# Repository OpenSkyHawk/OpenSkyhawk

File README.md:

```
  ____                ______        __ __            __  
 / __ \___  ___ ___  / __/ /____ __/ // /__ __    __/ /__
/ /_/ / _ \/ -_) _ \_\ \/  '_/ // / _  / _ `/ |/|/ /  '_/
\____/ .__/\__/_//_/___/_/\_\\_, /_//_/\_,_/|__,__/_/\_\ 
    /_/                     /___/                        
          ── DCS A-4E Skyhawk Home Cockpit ──
```

Physical DCS A-4E Skyhawk home cockpit — 3D-printed panels, custom PCBs, and STM32 firmware for the [DCS A-4E Community Mod](https://github.com/Community-A-4E/community-a4e-c). Controllers communicate over CAN bus.

## Repository Structure

```
OpenSkyhawk/
├── CAD/                        # Fusion 360 source files (.f3d); STLs gitignored
│   ├── Center_Console/
│   ├── Left_Console/
│   ├── Right_Console/
│   └── Shared/                 # Common brackets, mounting fixtures
│
├── PCB/                        # KiCad projects, one folder per board
│   ├── Center_Console/
│   │   └── Center_Armament/
│   │       ├── Armament_MCU/   # Main STM32 board
│   │       ├── AWRS_Panel/     # Breakout board
│   │       └── Misc_Switch_Panel/
│   ├── Left_Console/
│   ├── Right_Console/
│   └── Libraries/              # Shared KiCad symbols and footprints
│
├── Firmware/                   # PlatformIO projects
│   ├── Panels/                 # Production sketches, one folder per node
│   ├── Templates/              # Starting points for new sketches
│   ├── Examples/               # Bench and end-to-end test sketches
│   └── Libraries/              # Shared firmware code
│
└── docs/
    ├── References/             # Cockpit photos, manuals, screenshots
    ├── Datasheets/             # Component datasheets
    └── claude/                 # AI-readable architecture and standards docs
```

## Architecture

Each physical panel group is driven by one **STM32F103CBT6** MCU board. Boards communicate over **CAN bus** via Molex Mini-Fit Jr connectors. Panel breakout boards connect to their MCU board via 6- or 8-pin JST-XH harnesses. Firmware is built with **PlatformIO**.

DCS communication: DCS-BIOS cockpit state flows PC → USB CDC → RP2040 bridge (Tiny2040) → UART → STM32 CAN master → CAN bus → all avionics nodes. STM32 native USB CDC is not used — it crashes under sustained DCS-BIOS load.

## Console Layout

| Console | Panels |
|---------|--------|
| Center Console | Armament, AWRS, Misc Switches, main flight instruments |
| Left Console | ECM, fuel, electrical systems |
| Right Console | Radios, nav |

## Hardware Notes

### Screw Standards

| Size | Use |
|------|-----|
| M2 | PCB mounts, small standoffs |
| M3 | Placards, light rings, small brackets |
| M4 | Instrument bezels, gauge mounting — clearance Ø4.3–4.5 mm |
| M5 | Panel-to-subpanel, corner mounts — clearance Ø5.3–5.5 mm |

### Switch Sizing

- Toggle switches: 12 mm (standard panels), ~6 mm (ECM modules)

### Gauges

- LOX gauge: 2-5/8″ (~67 mm total)
- Radar Altimeter: 3-1/8″ (~100 mm total with bezel)

## Licensing

Copyright (c) 2026 OpenSkyHawk.

| Layer | License |
|-------|---------|
| CAD, PCB, Docs | CC BY-NC-SA 4.0 — root [LICENSE](./LICENSE) |
| Firmware | GPL v2 (DCS-BIOS dependency) — [Firmware/LICENSE](./Firmware/LICENSE) |

GitHub's repo-level badge reflects the root `LICENSE` (CC BY-NC-SA 4.0); the
firmware is GPL v2 under `Firmware/LICENSE`.

## References

- [Open Hornet Hardware](https://github.com/jrsteensen/OpenHornet)
- [Open Hornet Software](https://github.com/jrsteensen/OpenHornet-Software)
- [The Warthog Project](https://thewarthogproject.com/)
- [Viperpits](https://www.viperpits.org/smf/index.php)
- [The Skyhawk Association — Cockpit](https://skyhawk.org/page/skyhawk-cockpit)

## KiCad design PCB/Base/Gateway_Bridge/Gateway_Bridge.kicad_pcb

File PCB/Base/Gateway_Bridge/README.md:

# Gateway_Bridge — Gateway/Bridge board (SimGateway + PanelBridge)

**Status: In progress** — not released yet.

A board is released only once it has been built, brought up, and verified: it is then listed in `PCB/manifest.yaml` and ships in the next hardware release (`hardware-vX.Y.Z`, see the repository's Releases). The model is design decision D10; the release standard is the *Releases* section of `docs/_source/hardware-standards.md`.

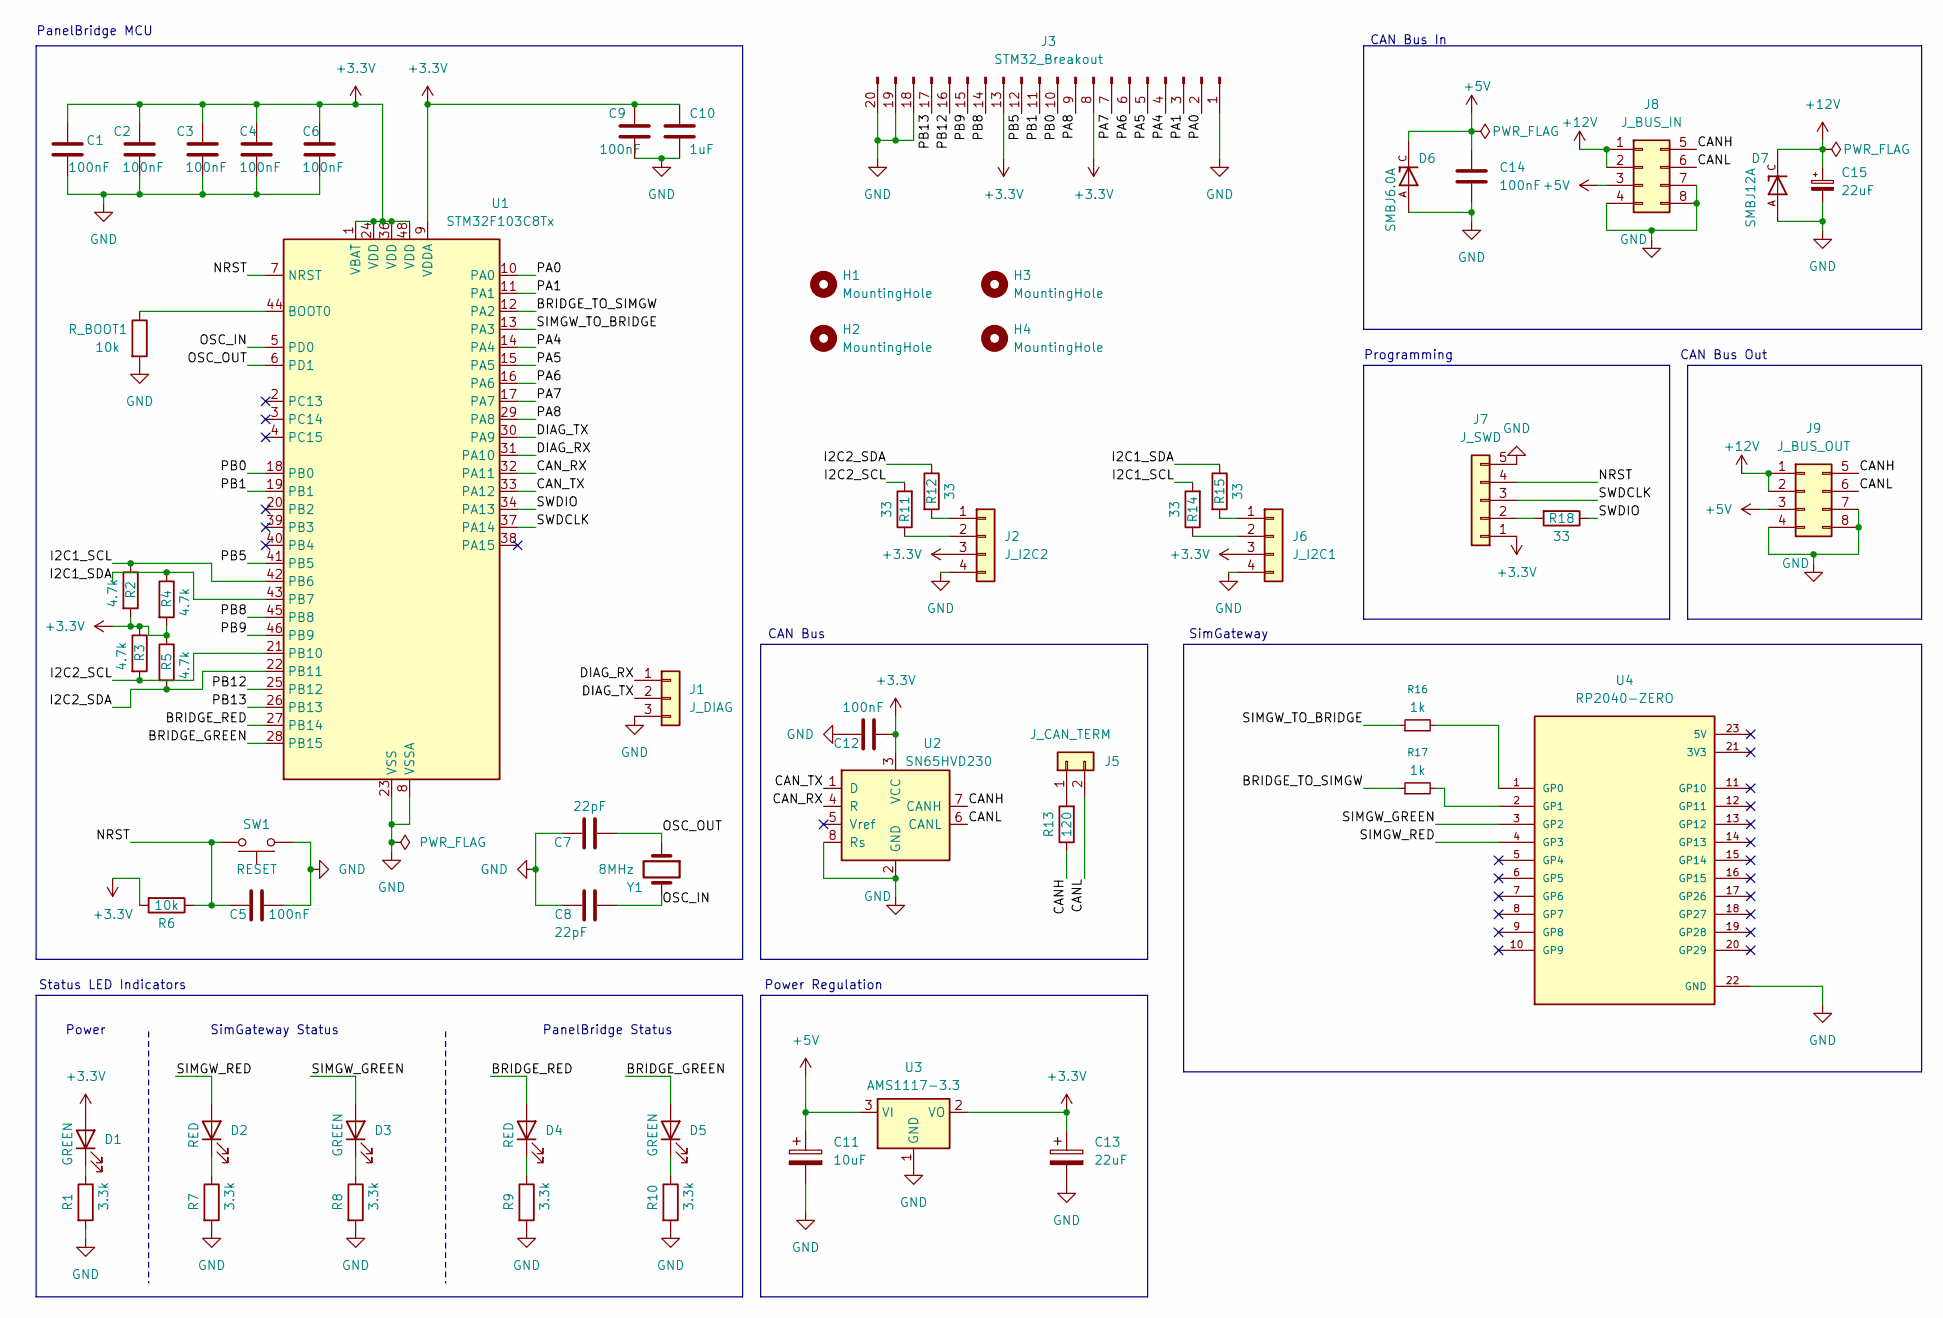
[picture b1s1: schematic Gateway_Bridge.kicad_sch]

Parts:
C1, C2, C3, C4, C5, C6, C9, C12, C14: 100nF; C_0805_2012Metric; Rating 50V; Tolerance 10%; LCSC C1711
C7, C8: 22pF; C_0805_2012Metric; Rating 50V; Tolerance 5%; LCSC C1804
C10: 1uF; C_0805_2012Metric; Rating 50V; Tolerance 10%; LCSC C28323
C11: 10uF; CP_Elec_4x5.4; Rating 25V; Tolerance 20%; LCSC C3343
C13: 22uF; CP_Elec_4x5.4; Rating 16V; Tolerance 20%; LCSC C72502
C15: 22uF; CP_Elec_5x5.4; Rating 35V; Tolerance 20%; LCSC C48971029
D1, D3, D5: GREEN; LED_0805_2012Metric; LCSC C19171393
D2, D4: RED; LED_0805_2012Metric; LCSC C19171391
D6: SMBJ6.0A; DIOM4336X265N; PARTREV NA; LCSC C5331096
D7: SMBJ12A; DIOM4336X265N; PARTREV F2102; LCSC C42368008
H1, H2, H3, H4: MountingHole; MountingHole_2.7mm_M2.5
J1: J_DIAG; JST_XH_B3B-XH-A_1x03_P2.50mm_Vertical; LCSC C51940188
J2: J_I2C2; JST_XH_B4B-XH-A_1x04_P2.50mm_Vertical; LCSC C23067544
J3: STM32_Breakout; PinHeader_1x20_P2.54mm_Vertical
J5: J_CAN_TERM; PinHeader_1x02_P2.54mm_Vertical
J6: J_I2C1; JST_XH_B4B-XH-A_1x04_P2.50mm_Vertical; LCSC C23067544
J7: J_SWD; PinHeader_1x05_P2.54mm_Vertical
J8: J_BUS_IN; Molex_Mini-Fit_Jr_5566-08A_2x04_P4.20mm_Vertical; LCSC C20608116
J9: J_BUS_OUT; Molex_Mini-Fit_Jr_5566-08A_2x04_P4.20mm_Vertical; LCSC C20608116
R1, R7, R8, R9, R10: 3.3k; R_0805_2012Metric; Rating 1/8W; Tolerance 1%; LCSC C844412
R2, R3, R4, R5: 4.7k; R_0805_2012Metric; Rating 1/8W; Tolerance 1%; LCSC C844941
R6: 10k; R_0805_2012Metric; Rating 1/8W; Tolerance 1%; LCSC C844937
R11, R12, R14, R15, R18: 33; R_0805_2012Metric; Rating 1/8W; Tolerance 1%; LCSC C2090807
R13: 120; R_0805_2012Metric; Rating 1/8W; Tolerance 1%; LCSC C844816
R16, R17: 1k; R_0805_2012Metric; Rating 1/8W; Tolerance 1%; LCSC C844939
R_BOOT1: 10k; R_0805_2012Metric; Rating 1/8W; Tolerance 1%; LCSC C844937
SW1: RESET; SW_PUSH_6mm; LCSC C2939600
U1: STM32F103C8Tx; LQFP-48_7x7mm_P0.5mm; LCSC C8734
U2: SN65HVD230; SOIC-8_3.9x4.9mm_P1.27mm; LCSC C12084
U3: AMS1117-3.3; SOT-223-3_TabPin2; LCSC C347222
U4: RP2040-ZERO; MODULE_RP2040-ZERO; PARTREV NA
Y1: 8MHz; Crystal_SMD_5032-2Pin_5.0x3.2mm; LCSC C20617997

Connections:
+3.3V: C1.1, C2.1, C3.1, C4.1, C6.1, C9.1, C10.1, C12.1, C13.1, D1.2 (A), J2.3, J3.8, J3.13, J6.3, J7.1, R2.2, R3.1, R4.2, R5.1, R6.2, U1.1 (VBAT), U1.9 (VDDA), U1.24 (VDD), U1.36 (VDD), U1.48 (VDD), U2.3 (VCC), U3.2 (VO)
+5V: C11.1, C14.1, D6.C, J8.3, J9.3, U3.3 (VI)
+12V: C15.1, D7.C, J8.1, J8.2, J9.1, J9.2
/BRIDGE_GREEN: D5.2 (A), U1.28 (PB15)
/BRIDGE_RED: D4.2 (A), U1.27 (PB14)
/BRIDGE_TO_SIMGW: R17.1, U1.12 (PA2)
/CANH: J8.5, J9.5, R13.1, U2.7 (CANH)
/CANL: J5.2, J8.6, J9.6, U2.6 (CANL)
/CAN_RX: U1.32 (PA11), U2.4 (R)
/CAN_TX: U1.33 (PA12), U2.1 (D)
/DIAG_RX: J1.1, U1.31 (PA10)
/DIAG_TX: J1.2, U1.30 (PA9)
/I2C1_SCL: R2.1, R14.2, U1.42 (PB6)
/I2C1_SDA: R4.1, R15.1, U1.43 (PB7)
/I2C2_SCL: R3.2, R11.2, U1.21 (PB10)
/I2C2_SDA: R5.2, R12.1, U1.22 (PB11)
/NRST: C5.1, J7.4, R6.1, SW1.2, U1.7 (NRST)
/OSC_IN: C8.1, U1.5 (PD0), Y1.2
/OSC_OUT: C7.2, U1.6 (PD1), Y1.1
/PA0: J3.2, U1.10 (PA0)
/PA1: J3.3, U1.11 (PA1)
/PA4: J3.4, U1.14 (PA4)
/PA5: J3.5, U1.15 (PA5)
/PA6: J3.6, U1.16 (PA6)
/PA7: J3.7, U1.17 (PA7)
/PA8: J3.9, U1.29 (PA8)
/PB0: J3.10, U1.18 (PB0)
/PB1: J3.11, U1.19 (PB1)
/PB5: J3.12, U1.41 (PB5)
/PB8: J3.14, U1.45 (PB8)
/PB9: J3.15, U1.46 (PB9)
/PB12: J3.16, U1.25 (PB12)
/PB13: J3.17, U1.26 (PB13)
/SIMGW_GREEN: D3.2 (A), U4.3 (GP2)
/SIMGW_RED: D2.2 (A), U4.4 (GP3)
/SIMGW_TO_BRIDGE: R16.1, U1.13 (PA3)
/SWDCLK: J7.3, U1.37 (PA14)
/SWDIO: R18.1, U1.34 (PA13)
GND: C1.2, C2.2, C3.2, C4.2, C5.2, C6.2, C7.1, C8.2, C9.2, C10.2, C11.2, C12.2, C13.2, C14.2, C15.2, D6.A, D7.A, J1.3, J2.4, J3.1, J3.18, J3.19, J3.20, J6.4, J7.5, J8.4, J8.7, J8.8, J9.4, J9.7, J9.8, R1.2, R7.2, R8.2, R9.2, R10.2, R_BOOT1.2, SW1.1, U1.8 (VSSA), U1.23 (VSS), U1.35 (VSS), U1.47 (VSS), U2.2 (GND), U2.8 (Rs), U3.1 (GND), U4.22 (GND)
unnamed: D1.1 (K), R1.1
unnamed: D2.1 (K), R7.1
unnamed: D3.1 (K), R8.1
unnamed: D4.1 (K), R9.1
unnamed: D5.1 (K), R10.1
unnamed: J2.1, R12.2
unnamed: J2.2, R11.1
unnamed: J5.1, R13.2
unnamed: J6.1, R15.2
unnamed: J6.2, R14.1
unnamed: J7.2, R18.2
unnamed: R_BOOT1.1, U1.44 (BOOT0)
unnamed: R16.2, U4.1 (GP0)
unnamed: R17.2, U4.2 (GP1)

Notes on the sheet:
Power Regulation
PanelBridge Status
SimGateway Status
Programming
SimGateway
PanelBridge MCU
CAN Bus Out
Power
CAN Bus In
CAN Bus
Status LED Indicators

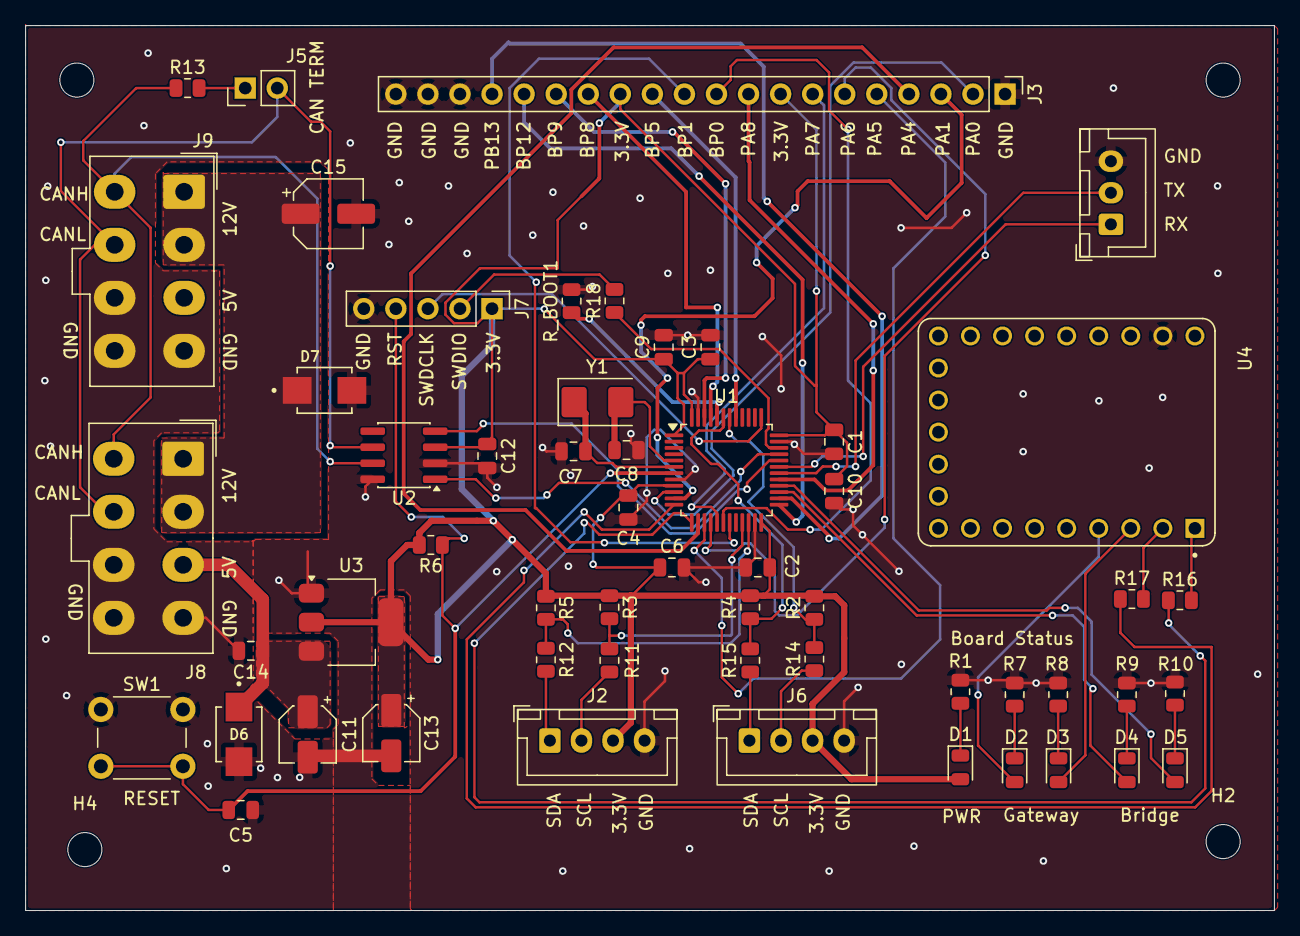
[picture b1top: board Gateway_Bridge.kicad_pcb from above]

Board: 2 copper layers, 98.9 x 70.1 mm, 59 parts (0 on the bottom side), 53 nets.

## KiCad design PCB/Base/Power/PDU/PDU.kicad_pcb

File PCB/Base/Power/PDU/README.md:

# PDU — power distribution unit

**Status: In progress** — not released yet.

A board is released only once it has been built, brought up, and verified: it is then listed in `PCB/manifest.yaml` and ships in the next hardware release (`hardware-vX.Y.Z`, see the repository's Releases). The model is design decision D10; the release standard is the *Releases* section of `docs/_source/hardware-standards.md`.

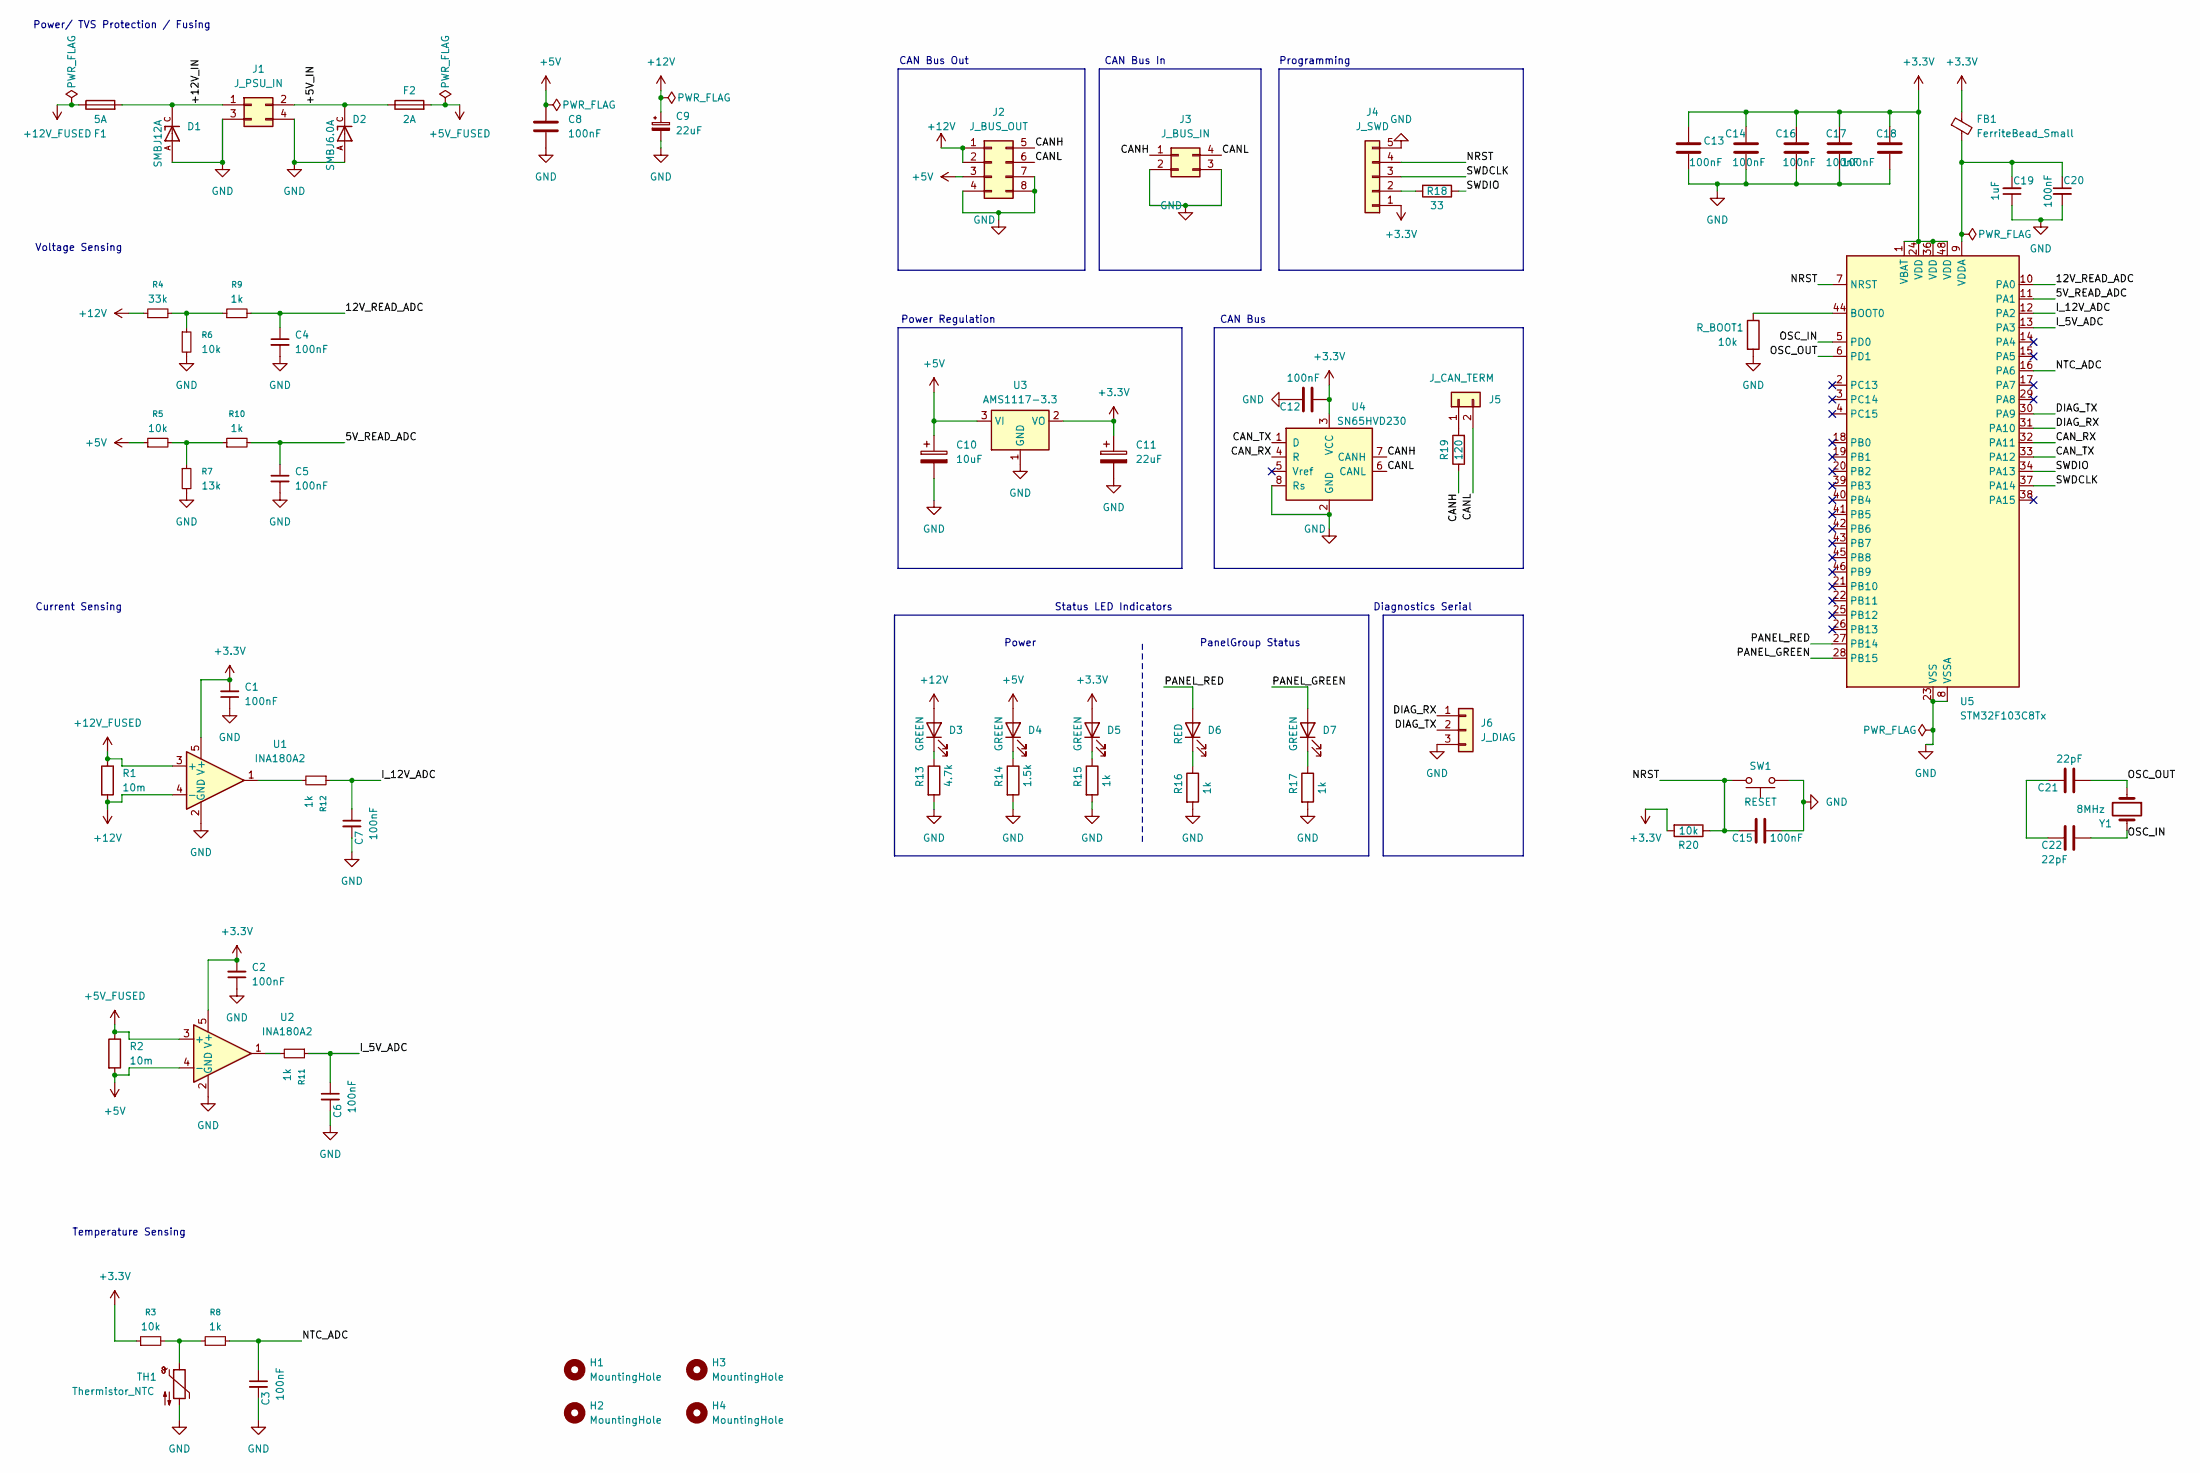
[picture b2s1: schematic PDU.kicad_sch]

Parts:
C1, C2, C3, C4, C5, C6, C7, C8, C12, C13, C14, C15, C16, C17, C18, C20: 100nF; C_0805_2012Metric; Rating 50V; Tolerance 10%; LCSC C1711
C9: 22uF; CP_Elec_5x5.4; Rating 35V; Tolerance 20%; LCSC C48971029
C10: 10uF; CP_Elec_4x5.4; Rating 25V; Tolerance 20%; LCSC C3343
C11: 22uF; CP_Elec_4x5.4; Rating 16V; Tolerance 20%; LCSC C72502
C19: 1uF; C_0805_2012Metric; Rating 50V; Tolerance 10%; LCSC C28323
C21, C22: 22pF; C_0805_2012Metric; Rating 50V; Tolerance 5%; LCSC C1804
D1: SMBJ12A; DIOM4336X265N; PARTREV F2102; LCSC C42368008
D2: SMBJ6.0A; DIOM4336X265N; PARTREV NA; LCSC C5331096
D3, D4, D5, D7: GREEN; LED_0805_2012Metric; LCSC C19171393
D6: RED; LED_0805_2012Metric; LCSC C19171391
F1: 5A; FUSE-TH_4P-L16.0-W6.7; LCSC C19727305
F2: 2A; FUSE-TH_4P-L16.0-W6.7; LCSC C19727305
FB1: FerriteBead_Small; L_0805_2012Metric; LCSC C21519
H1, H2, H3, H4: MountingHole; MountingHole_2.7mm_M2.5
J1: J_PSU_IN; Molex_Mini-Fit_Jr_5566-04A_2x02_P4.20mm_Vertical; LCSC C20608114
J2: J_BUS_OUT; Molex_Mini-Fit_Jr_5566-08A_2x04_P4.20mm_Vertical; LCSC C20608116
J3: J_BUS_IN; Molex_Mini-Fit_Jr_5566-04A_2x02_P4.20mm_Vertical; LCSC C20608114
J4: J_SWD; PinHeader_1x05_P2.54mm_Vertical
J5: J_CAN_TERM; PinHeader_1x02_P2.54mm_Vertical
J6: J_DIAG; JST_XH_B3B-XH-A_1x03_P2.50mm_Vertical; LCSC C51940188
R1, R2: 10m; R_2512_6332Metric; Rating 3W; Tolerance 1%; LCSC C2903468
R3, R5: 10k; R_0805_2012Metric; Rating 1/8W; Tolerance 1%; LCSC C844937
R4: 33k; R_0805_2012Metric; Rating 1/8W; Tolerance 0.1%; LCSC C2828767
R6, R20: 10k; R_0805_2012Metric; Rating 1/8W; Tolerance 0.1%; LCSC C406725
R7: 13k; R_0805_2012Metric; Rating 1/8W; Tolerance 0.1%; LCSC C865184
R8, R9, R10, R11, R12, R15, R16, R17: 1k; R_0805_2012Metric; Rating 1/8W; Tolerance 1%; LCSC C844939
R13: 4.7k; R_0805_2012Metric; Rating 1/8W; Tolerance 1%; LCSC C844941
R14: 1.5k; R_0805_2012Metric; Rating 1/8W; Tolerance 1%; LCSC C49254235
R18: 33; R_0805_2012Metric; Rating 1/8W; Tolerance 1%; LCSC C2090807
R19: 120; R_0805_2012Metric; Rating 1/8W; Tolerance 1%; LCSC C844816
R_BOOT1: 10k; R_0805_2012Metric; Rating 1/8W; Tolerance 1%; LCSC C844937
SW1: RESET; SW_PUSH_6mm; LCSC C2939600
TH1: Thermistor_NTC; R_1206_3216Metric; Tolerance 1%; LCSC C52155460
U1, U2: INA180A2; SOT-23-5; LCSC C192764
U3: AMS1117-3.3; SOT-223-3_TabPin2; LCSC C347222
U4: SN65HVD230; SOIC-8_3.9x4.9mm_P1.27mm; LCSC C12084
U5: STM32F103C8Tx; LQFP-48_7x7mm_P0.5mm; LCSC C8734
Y1: 8MHz; Crystal_SMD_5032-2Pin_5.0x3.2mm; LCSC C20617997

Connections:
+3.3V: C1.2, C2.2, C11.1, C12.1, C13.1, C14.1, C16.1, C17.1, C18.1, D5.2 (A), FB1.1, J4.1, R3.1, R20.2, U1.5 (V+), U2.5 (V+), U3.2 (VO), U4.3 (VCC), U5.1 (VBAT), U5.24 (VDD), U5.36 (VDD), U5.48 (VDD)
+5V: C8.1, C10.1, D4.2 (A), J2.3, R2.2, R5.1, U2.4 (-), U3.3 (VI)
+5V_FUSED: F2.2, R2.1, U2.3 (+)
+12V: C9.1, D3.2 (A), J2.1, J2.2, R1.2, R4.1, U1.4 (-)
+12V_FUSED: F1.1, R1.1, U1.3 (+)
/5V_READ_ADC: C5.1, R10.2, U5.11 (PA1)
/12V_READ_ADC: C4.1, R9.2, U5.10 (PA0)
/+5V_IN: D2.C, F2.1, J1.2
/+12V_IN: D1.C, F1.2, J1.1
/CANH: J2.5, J3.1, R19.1, U4.7 (CANH)
/CANL: J2.6, J3.4, J5.2, U4.6 (CANL)
/CAN_RX: U4.4 (R), U5.32 (PA11)
/CAN_TX: U4.1 (D), U5.33 (PA12)
/DIAG_RX: J6.1, U5.31 (PA10)
/DIAG_TX: J6.2, U5.30 (PA9)
/I_5V_ADC: C6.1, R11.1, U5.13 (PA3)
/I_12V_ADC: C7.1, R12.1, U5.12 (PA2)
/NRST: C15.1, J4.4, R20.1, SW1.2, U5.7 (NRST)
/NTC_ADC: C3.1, R8.2, U5.16 (PA6)
/OSC_IN: C22.1, U5.5 (PD0), Y1.2
/OSC_OUT: C21.2, U5.6 (PD1), Y1.1
/PANEL_GREEN: D7.2 (A), U5.28 (PB15)
/PANEL_RED: D6.2 (A), U5.27 (PB14)
/SWDCLK: J4.3, U5.37 (PA14)
/SWDIO: R18.1, U5.34 (PA13)
GND: C1.1, C2.1, C3.2, C4.2, C5.2, C6.2, C7.2, C8.2, C9.2, C10.2, C11.2, C12.2, C13.2, C14.2, C15.2, C16.2, C17.2, C18.2, C19.1, C20.2, D1.A, D2.A, J1.3, J1.4, J2.4, J2.7, J2.8, J3.2, J3.3, J4.5, J6.3, R6.2, R7.2, R13.2, R14.2, R15.2, R16.2, R17.2, R_BOOT1.2, SW1.1, TH1.2, U1.2 (GND), U2.2 (GND), U3.1 (GND), U4.2 (GND), U4.8 (Rs), U5.8 (VSSA), U5.23 (VSS), U5.35 (VSS), U5.47 (VSS)
unnamed: C21.1, C22.2
unnamed: D3.1 (K), R13.1
unnamed: D4.1 (K), R14.1
unnamed: D5.1 (K), R15.1
unnamed: D6.1 (K), R16.1
unnamed: D7.1 (K), R17.1
unnamed: J4.2, R18.2
unnamed: J5.1, R19.2
unnamed: R3.2, R8.1, TH1.1
unnamed: R4.2, R6.1, R9.1
unnamed: R5.2, R7.1, R10.1
unnamed: R11.2, U2.1
unnamed: R12.2, U1.1
unnamed: R_BOOT1.1, U5.44 (BOOT0)
unnamed: C19.2, C20.1, FB1.2, U5.9 (VDDA)

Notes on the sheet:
Current Sensing
CAN Bus
Programming
Temperature Sensing
Diagnostics Serial
PanelGroup Status
Power Regulation
Power
Power/ TVS Protection / Fusing
Status LED Indicators
CAN Bus In
CAN Bus Out
Voltage Sensing

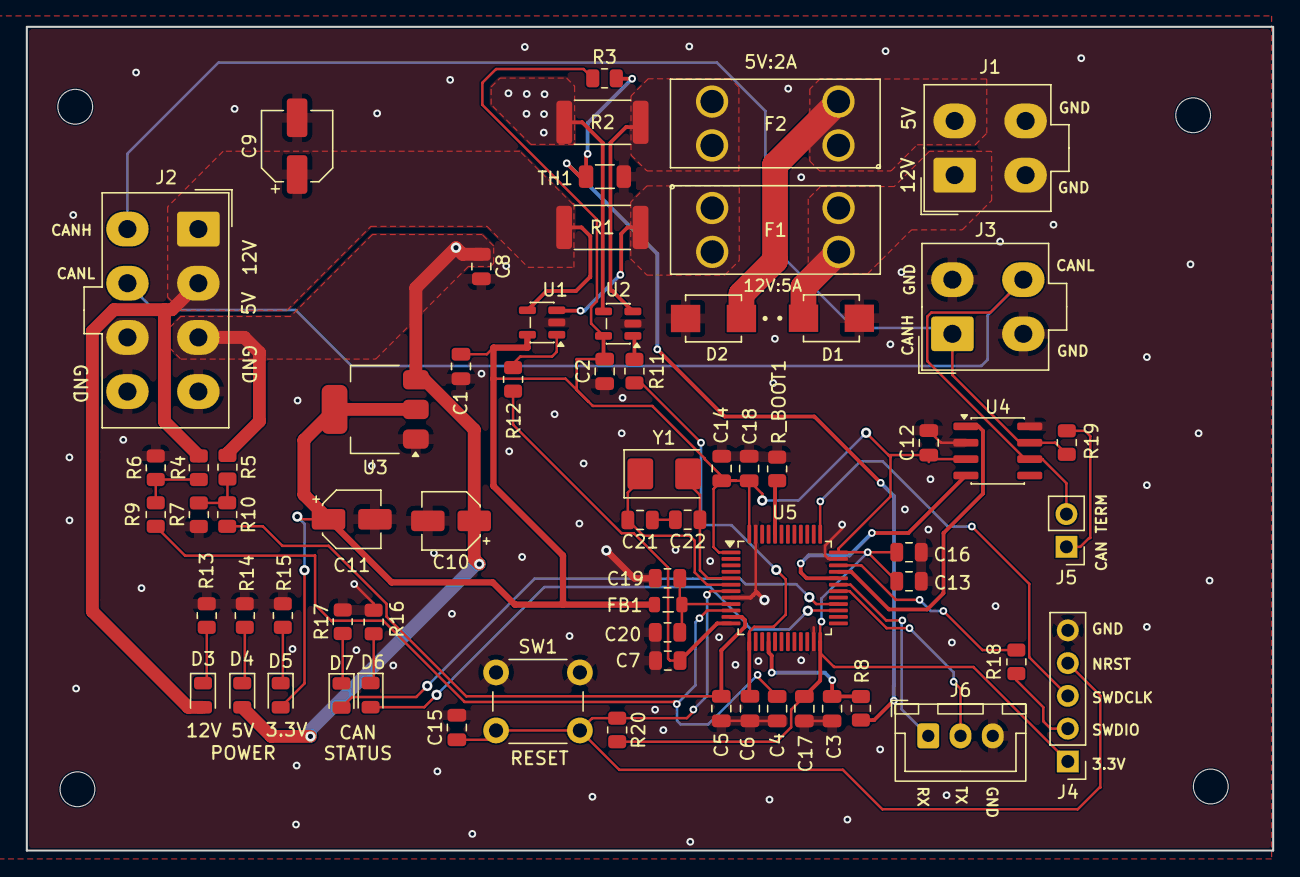
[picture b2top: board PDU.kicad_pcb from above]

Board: 2 copper layers, 96.6 x 63.9 mm, 71 parts (0 on the bottom side), 41 nets.

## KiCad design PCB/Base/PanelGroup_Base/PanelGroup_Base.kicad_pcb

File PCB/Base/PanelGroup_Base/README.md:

# PanelGroup_Base — PanelGroup base board

**Status: In progress** — not released yet.

A board is released only once it has been built, brought up, and verified: it is then listed in `PCB/manifest.yaml` and ships in the next hardware release (`hardware-vX.Y.Z`, see the repository's Releases). The model is design decision D10; the release standard is the *Releases* section of `docs/_source/hardware-standards.md`.

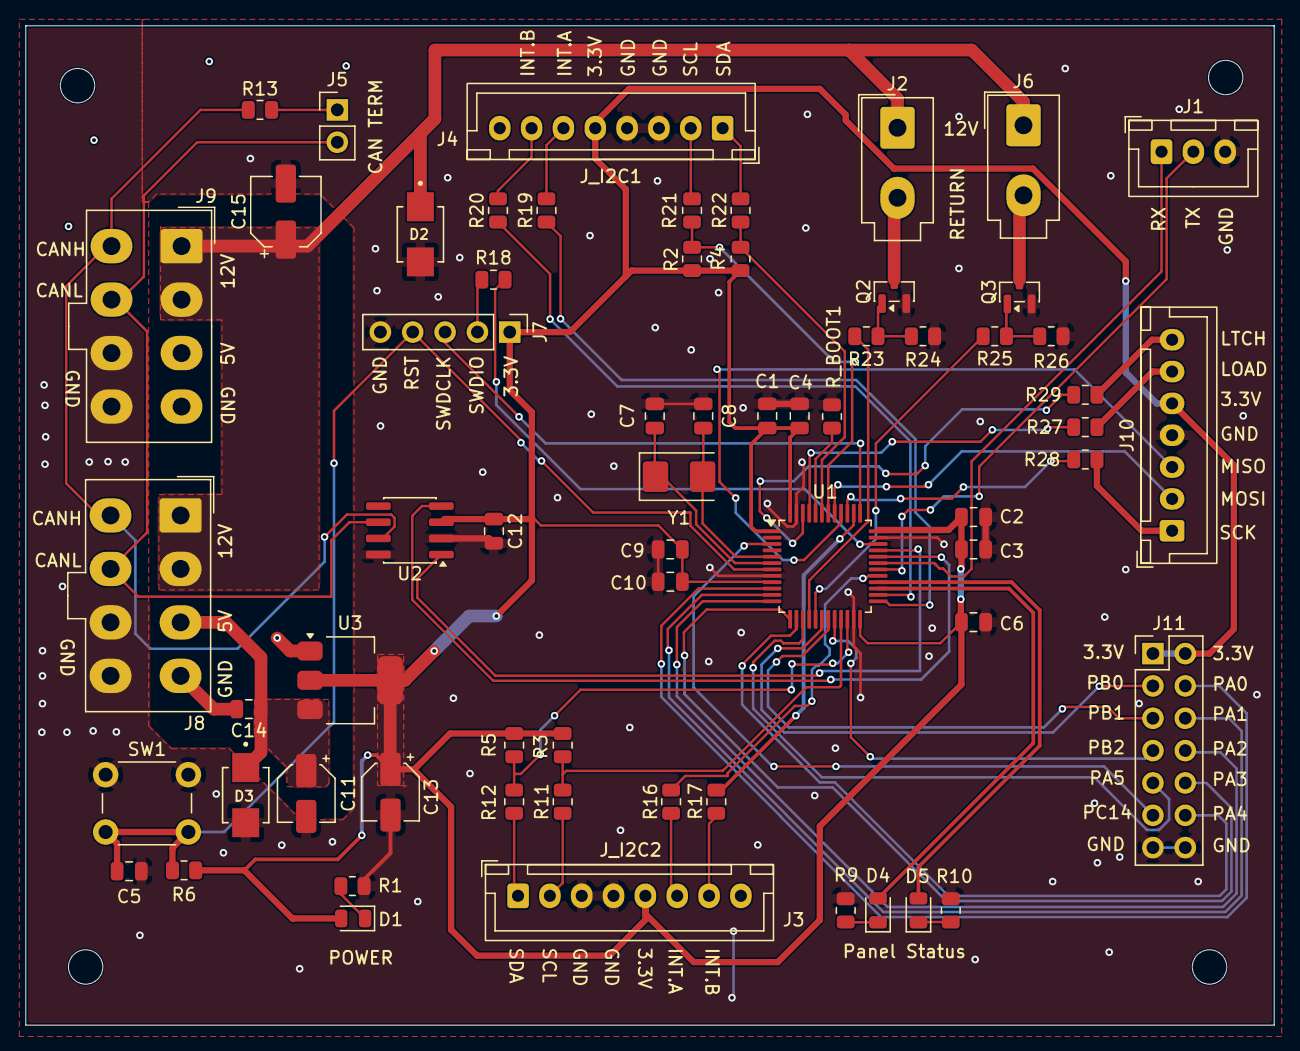
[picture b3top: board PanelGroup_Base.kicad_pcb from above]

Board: 2 copper layers, 98.0 x 78.5 mm, 68 parts (0 on the bottom side), 63 nets.

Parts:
C1, C2, C3, C4, C5, C6, C9, C12, C14: 100nF; C_0805_2012Metric
C7, C8: 22pF; C_0805_2012Metric
C10: 1uF; C_0805_2012Metric
C11: 10uF; CP_Elec_4x5.4
C13: 22uF; CP_Elec_4x5.4
C15: 22uF; CP_Elec_5x5.4
D1, D5: GREEN; LED_0805_2012Metric
D2: SMBJ12A; DIOM4336X265N
D3: SMBJ6.0A; DIOM4336X265N
D4: RED; LED_0805_2012Metric
H1, H2, H3, H4: MountingHole; MountingHole_2.7mm_M2.5
J1: J_DIAG; JST_XH_B3B-XH-A_1x03_P2.50mm_Vertical
J2: J_BL1; Molex_Mini-Fit_Jr_5566-02A_2x01_P4.20mm_Vertical
J3: J_I2C2; JST_XH_B8B-XH-A_1x08_P2.50mm_Vertical
J4: J_I2C1; JST_XH_B8B-XH-A_1x08_P2.50mm_Vertical
J5: J_CAN_TERM; PinHeader_1x02_P2.54mm_Vertical
J6: J_BL2; Molex_Mini-Fit_Jr_5566-02A_2x01_P4.20mm_Vertical
J7: J_SWD; PinHeader_1x05_P2.54mm_Vertical
J8: J_BUS_IN; Molex_Mini-Fit_Jr_5566-08A_2x04_P4.20mm_Vertical
J9: J_BUS_OUT; Molex_Mini-Fit_Jr_5566-08A_2x04_P4.20mm_Vertical
J10: J_SR; JST_XH_B7B-XH-A_1x07_P2.50mm_Vertical
J11: J_BREAKOUT; PinHeader_2x07_P2.54mm_Vertical
Q2, Q3: AO3400A; SOT-23
R1, R9, R10: 3.3k; R_0805_2012Metric
R2, R3, R4, R5: 4.7k; R_0805_2012Metric
R6: 10k; R_0805_2012Metric
R11, R12, R18, R21, R22, R27, R28, R29: 33; R_0805_2012Metric
R13: 120; R_0805_2012Metric
R16, R17, R19, R20, R23, R25: 100; R_0805_2012Metric
R24, R26: 100k; R_0805_2012Metric
R_BOOT1: 10k; R_0805_2012Metric
SW1: RESET; SW_PUSH_6mm
U1: STM32F103C8Tx; LQFP-48_7x7mm_P0.5mm
U2: SN65HVD230; SOIC-8_3.9x4.9mm_P1.27mm
U3: AMS1117-3.3; SOT-223-3_TabPin2
Y1: 8MHz; Crystal_SMD_5032-2Pin_5.0x3.2mm

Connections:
+3.3V: C1.1, C2.1, C3.1, C4.1, C6.1, C9.1, C10.1, C12.1, C13.1, D1.2 (A), J3.5, J4.5, J7.1, J10.5, J11.1, J11.2, R2.2, R3.1, R4.2, R5.1, R6.2, U1.1 (VBAT), U1.9 (VDDA), U1.24 (VDD), U1.36 (VDD), U1.48 (VDD), U2.3 (VCC), U3.2 (VO)
+5V: C11.1, C14.1, D3.C, J8.3, J9.3, U3.3 (VI)
+12V: C15.1, D2.C, J2.1, J6.1, J8.1, J8.2, J9.1, J9.2
/BL1_RETURN: J2.2, Q2.3
/BL2_RETURN: J6.2, Q3.3
/CANH: J8.5, J9.5, R13.1, U2.7 (CANH)
/CANL: J5.2, J8.6, J9.6, U2.6 (CANL)
/CAN_RX: U1.32 (PA11), U2.4 (R)
/CAN_TX: U1.33 (PA12), U2.1 (D)
/DIAG_RX: J1.1, U1.31 (PA10)
/DIAG_TX: J1.2, U1.30 (PA9)
/I2C1_SCL: R2.1, R21.2, U1.42 (PB6)
/I2C1_SDA: R4.1, R22.1, U1.43 (PB7)
/I2C2_SCL: R3.2, R11.2, U1.21 (PB10)
/I2C2_SDA: R5.2, R12.1, U1.22 (PB11)
/INT_A1: R19.1, U1.25 (PB12)
/INT_A2: R16.1, U1.29 (PA8)
/INT_B1: R20.1, U1.26 (PB13)
/INT_B2: R17.1, U1.38 (PA15)
/NRST: C5.1, J7.4, R6.1, SW1.2, U1.7 (NRST)
/OSC_IN: C8.1, U1.5 (PD0), Y1.2
/OSC_OUT: C7.2, U1.6 (PD1), Y1.1
/PA0: J11.4, U1.10 (PA0)
/PA1: J11.6, U1.11 (PA1)
/PA2: J11.8, U1.12 (PA2)
/PA3: J11.10, U1.13 (PA3)
/PA4: J11.12, U1.14 (PA4)
/PA5: J11.9, U1.15 (PA5)
/PANEL_GREEN: D5.2 (A), U1.28 (PB15)
/PANEL_RED: D4.2 (A), U1.27 (PB14)
/PB0: J11.3, U1.18 (PB0)
/PB1: J11.5, U1.19 (PB1)
/PB2: J11.7, U1.20 (PB2)
/PC14: J11.11, U1.3 (PC14)
/PWM_BL1: R23.1, U1.16 (PA6)
/PWM_BL2: R25.1, U1.17 (PA7)
/SR_LATCH: R29.2, U1.46 (PB9)
/SR_LOAD: R27.2, U1.45 (PB8)
/SR_MISO: J10.3, U1.40 (PB4)
/SR_MOSI: J10.2, U1.41 (PB5)
/SR_SCK: R28.2, U1.39 (PB3)
/SWDCLK: J7.3, U1.37 (PA14)
/SWDIO: R18.1, U1.34 (PA13)
GND: C1.2, C2.2, C3.2, C4.2, C5.2, C6.2, C7.1, C8.2, C9.2, C10.2, C11.2, C12.2, C13.2, C14.2, C15.2, D2.A, D3.A, J1.3, J3.3, J3.4, J4.3, J4.4, J7.5, J8.4, J8.7, J8.8, J9.4, J9.7, J9.8, J10.4, J11.13, J11.14, Q2.2, Q3.2, R1.2, R9.2, R10.2, R24.2, R26.2, R_BOOT1.2, SW1.1, U1.8 (VSSA), U1.23 (VSS), U1.35 (VSS), U1.47 (VSS), U2.2 (GND), U2.8 (Rs), U3.1 (GND)
unnamed: D1.1 (K), R1.1
unnamed: D4.1 (K), R9.1
unnamed: D5.1 (K), R10.1
unnamed: J3.1, R12.2
unnamed: J3.2, R11.1
unnamed: J3.6, R16.2
unnamed: J3.7, R17.2
unnamed: J4.1, R22.2
unnamed: J4.2, R21.1
unnamed: J4.6, R19.2
unnamed: J4.7, R20.2
unnamed: J5.1, R13.2
unnamed: J7.2, R18.2
unnamed: J10.1, R28.1
unnamed: J10.6, R27.1
unnamed: J10.7, R29.1
unnamed: Q2.1, R23.2, R24.1
unnamed: Q3.1, R25.2, R26.1
unnamed: R_BOOT1.1, U1.44 (BOOT0)

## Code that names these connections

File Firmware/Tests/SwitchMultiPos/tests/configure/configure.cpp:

// SwitchMultiPos — configure test
//
// configure() must emit nothing; poll() must be a no-op until forceReport() runs once.
// Verified via emitCount(). CAN runs in NORMAL mode — the node ACKs the (unmodified) PanelBridge.
//
// Rig: STM32 on the CAN bus with the PanelBridge. Jumper PB0->PA0, PB1->PA1, PB4->PA4, PB5->PA5.

#include <Arduino.h>
#include <STM32Board.h>
#include <Inputs/SwitchMultiPos/SwitchMultiPos.h>

static constexpr uint16_t CTRL_ID = 0x5678;
static constexpr uint8_t  N       = 4;
static const uint8_t SW_PINS[N]   = { PA0, PA1, PA4, PA5 };
static const uint8_t CTRL_PINS[N] = { PB0, PB1, PB4, PB5 };

static void setActive(uint8_t idx) {
    for (uint8_t i = 0; i < N; i++) digitalWrite(CTRL_PINS[i], i == idx ? LOW : HIGH);
    delayMicroseconds(100);
}
static void txPush() { CANProtocol::flushBatched(canIdEvt(NODE_ID)); }   // push EVTs to the bridge

static const PinRef gPins[N] = { PinRef(SW_PINS[0]), PinRef(SW_PINS[1]), PinRef(SW_PINS[2]), PinRef(SW_PINS[3]) };
OpenSkyhawk::SwitchMultiPos gSel(CTRL_ID, gPins, N);

void setup() {
    STM32Board::setDebug(true);
    STM32Board::begin();
    STM32Board::diagSerial().println("=== SwitchMultiPos configure ===");

    bool pass = true;
    auto check = [&](const char* label, bool ok) {
        if (!ok) pass = false;
        STM32Board::diagSerial().print(label);
        STM32Board::diagSerial().println(ok ? ": PASS" : ": FAIL");
    };

    for (uint8_t i = 0; i < N; i++) pinMode(CTRL_PINS[i], OUTPUT);
    setActive(0);
    gSel.configure();
    CANProtocol::start();

    check("configure() emits no EVT", gSel.emitCount() == 0);

    gSel.poll();
    check("poll() before forceReport() is a no-op", gSel.emitCount() == 0);

    gSel.forceReport();
    txPush();
    check("forceReport() then emits once (index 0)", gSel.emitCount() == 1 && gSel.position() == 0);

    STM32Board::diagSerial().println(pass ? "=== ALL PASS ===" : "=== FAIL ===");
}

void loop() {}

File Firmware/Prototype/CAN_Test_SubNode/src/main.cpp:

// CAN_Test_SubNode — STM32F103CBT6
//
// Node ID from PA0 strap: HIGH (tied to 3.3V) → node_id=1,
//                         LOW  (internal pull-down) → node_id=2.
//
// CAN1 (PA11 RX / PA12 TX) @ 500 kbps.
// DiagSerial: USART1 PA9 TX / PA10 RX @ 115200.
//
// PB1 button: sends INPUT_EVENT (controlId 0x0001) to CAN bus on state change.
// Heartbeat and CAN health managed by PanelGroup::loop().

#include <PanelGroup.h>

static constexpr uint8_t BTN_PIN = PB1;
static bool lastBtnState = HIGH;

static void checkButton() {
    bool state = digitalRead(BTN_PIN);
    if (state == lastBtnState) return;
    lastBtnState = state;
    CANProtocol::sendBatched(canIdEvt(NODE_ID), ControlPacket{0x0001, (uint16_t)((state == LOW) ? 1 : 0)});
}

void setup() {
    pinMode(BTN_PIN, INPUT_PULLUP);
    PanelGroup::setup();
}

void loop() {
    PanelGroup::loop();
    checkButton();
}

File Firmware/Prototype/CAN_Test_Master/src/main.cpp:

// CAN_Test_Master — STM32F103CBT6
//
// Serial = UART2 (PA2/PA3) @ 250000 — RP2040 SimGateway link
// CAN1   PA11/PA12 @ 500 kbps — SN65HVD230 transceiver

#define DCSBIOS_DEFAULT_SERIAL
#include <DcsBios.h>
#include <PanelBridge.h>

void setup() {
    PanelBridge::setup();
    DcsBios::setup();
}

void loop() {
    DcsBios::loop();
    PanelBridge::loop();
}
